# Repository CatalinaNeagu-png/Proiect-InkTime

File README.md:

# Proiect-InkTime
## 1. Diagrama Bloc a Sistemului
Diagrama de mai jos arata cum sunt conectate componentele principale la microcontroller-ul nRF52840:

- **Alimentare:** USB-C -> BQ25180 (Charger) -> Baterie LiPo 400mAh.
- **Afisaj:** Ecran E-Paper 1.54 inch (Conectat prin SPI).
- **Senzori:** Accelerometru BMA423 (Conectat prin I2C).
- **Haptica:** Driver DRV2605 + Motor Vibratii (Conectat prin I2C).
- **Interactiune:** 3 Butoane Tactile (Conectate prin GPIO).

## 2. Bill of Materials (BOM)
Componente selectate din catalogul JLCPCB:

| Componenta | Producator | JLC Part Number | Datasheet |
| :--- | :--- | :--- | :--- |
| MCU nRF52840 | Nordic Semi | C190733 | [Datasheet](https://infocenter.nordicsemi.com/pdf/nRF52840_PS_v1.0.pdf) |
| Senzor BMA423 | Bosch | C404044 | [Datasheet](https://www.bosch-sensortec.com/media/boschsensortec/downloads/datasheets/bst-bma423-ds004.pdf) |
| Charger BQ25180 | TI | C2907481 | [Datasheet](https://www.ti.com/lit/ds/symlink/bq25180.pdf) |
| Driver DRV2605L | TI | C63523 | [Datasheet](https://www.ti.com/lit/ds/symlink/drv2605l.pdf) |
| Antena 2.45GHz | Johanson | C105252 | [Datasheet](https://www.johansontechnology.com/datasheets/2450AT18B100.pdf) |

## 3. Functionalitate Hardware
Dispozitivul foloseste nRF52840 pentru gestionarea comunicatiei Bluetooth Low Energy.

- **Display E-Paper:** Foloseste interfata **SPI**. Avantajul principal este consumul de energie zero cand imaginea este statica.
- **Senzori:** Accelerometrul BMA423 (interfata **I2C**) detecteaza miscarea si pasii.
- **Haptica:** Driverul DRV2605L (interfata **I2C**) controleaza motorul de vibratii pentru alerte.
- **Consum:** S-a calculat un consum in standby de aproximativ 20uA, ceea ce asigura o durata de viata a bateriei de peste 30 de zile.

## 4. Mapare Pini nRF52840

| Functie | Pin nRF | Interfata | Justificare |
| :--- | :--- | :--- | :--- |
| SPI SCK | P0.20 | SPI | Ceas pentru ecran |
| SPI MOSI | P0.21 | SPI | Date pentru ecran |
| SPI CS | P0.22 | SPI | Selectie ecran |
| I2C SDA | P0.26 | I2C | Date senzori/charger |
| I2C SCL | P0.27 | I2C | Ceas senzori/charger |
| Buton Sus | P0.11 | GPIO | Intrare navigare |
| Buton OK | P0.12 | GPIO | Intrare selectie |
| Buton Jos | P0.13 | GPIO | Intrare navigare |

## 5. Design si Integrare Mecanica
- **Aliniere:** Butoanele tactile sunt plasate la Y=3mm pentru a se potrivi cu decupajele carcasei WearAware.
- **Antena:** Are o zona dedicata "keep-out" fara cupru pentru a nu bloca semnalul Bluetooth.
- **Asamblare:** Componentele sunt asezate tip "sandwich": Carcasa -> Display -> PCB -> Baterie.

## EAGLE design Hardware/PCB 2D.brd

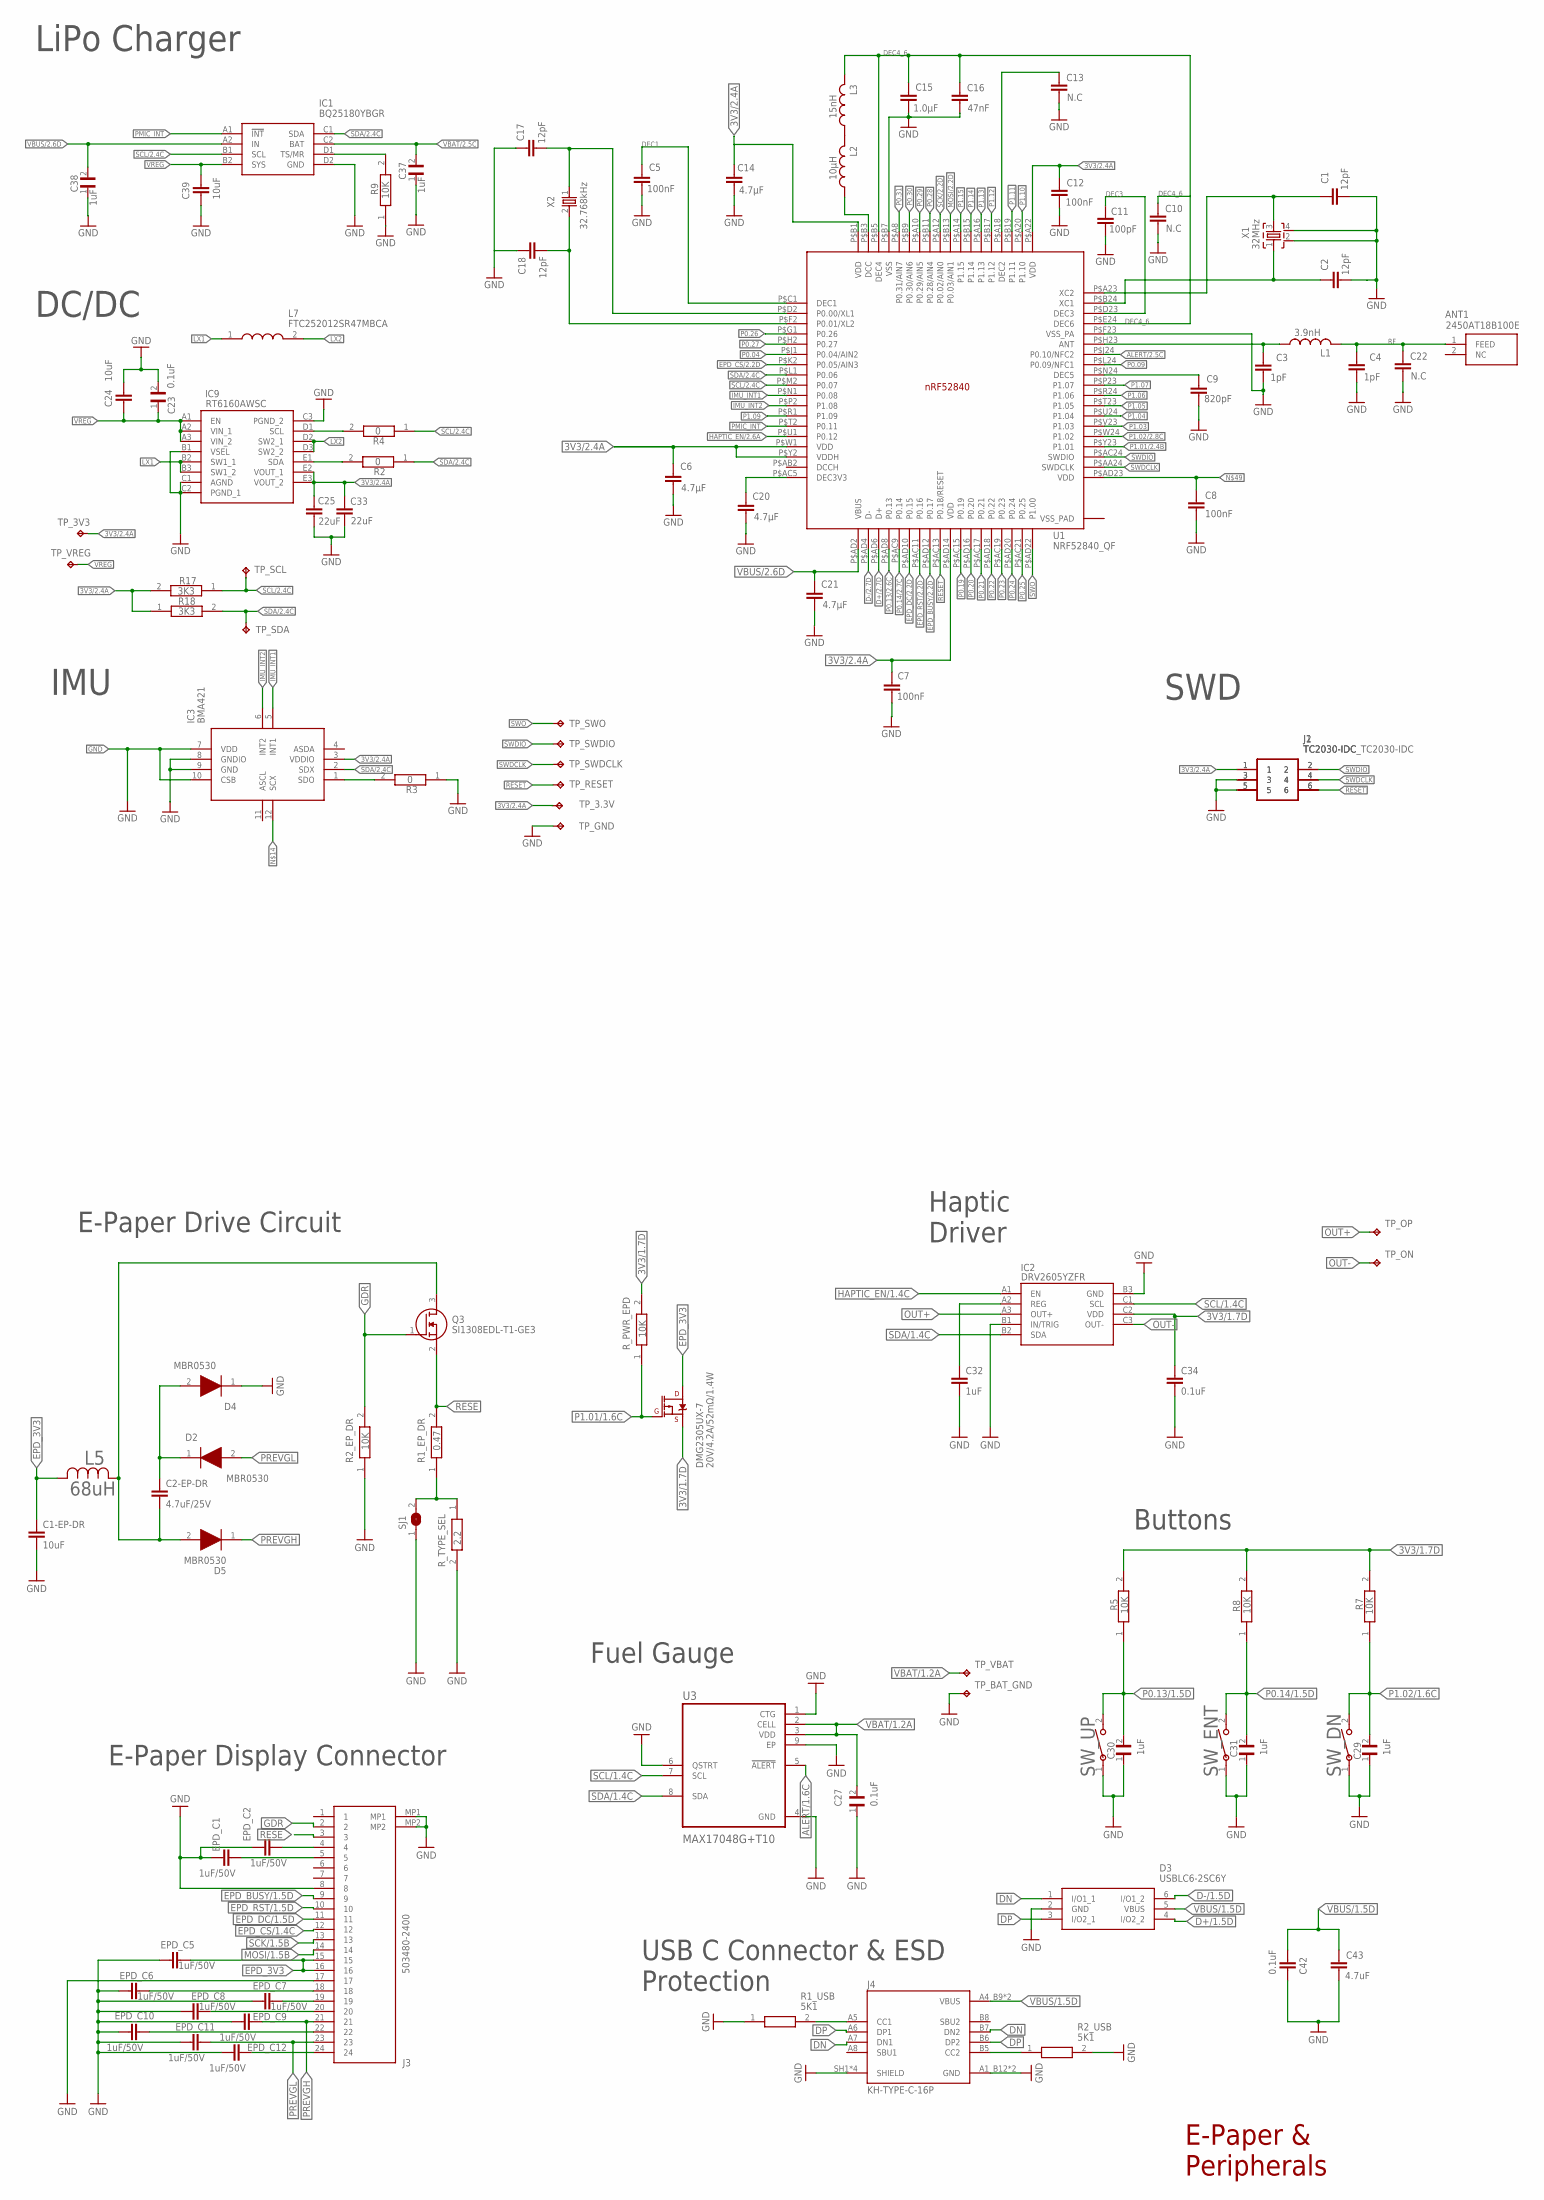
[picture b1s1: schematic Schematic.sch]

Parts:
ANT1: 2450AT18B100E; 2450AT18B100E_ANTC3216X140N
C1, C2, C17, C18: 12pF; NORDIC_NRF_3_RESC0201_L
C1-EP-DR: 10uF; ESP32_C6_LIBRARY_1_ESP32_WROVER_EAGLE-LTSPICE_C0402
C2-EP-DR: 4.7uF/25V; ESP32_C6_LIBRARY_1_ESP32_WROVER_EAGLE-LTSPICE_C0402
C3, C4: 1pF; NORDIC_NRF_3_RESC0201_L
C5, C7, C8, C12: 100nF; NORDIC_NRF_3_RESC0201_L
C6, C14, C20, C21: 4.7µF; NORDIC_NRF_3_RESC0201_L
C9: 820pF; NORDIC_NRF_3_RESC0201_L
C10, C13, C22: N.C; NORDIC_NRF_3_RESC0201_L
C11: 100pF; NORDIC_NRF_3_RESC0201_L
C15: 1.0µF; NORDIC_NRF_3_RESC0201_L
C16: 47nF; NORDIC_NRF_3_RESC0201_L
C23: 0.1uF; GRM011R60J152KE01L_1_0201
C24, C39: 10uF; NORDIC_NRF_3_RESC0201_L
C25, C33: 22uF; NORDIC_NRF_3_RESC0201_L
C27: 0.1uF; GRM011R60J152KE01L_2_CAPC0201X13N
C29, C30, C31: 1uF; GRM011R60J152KE01L_2_CAPC0201X13N
C32: 1uF; ESP32_C6_LIBRARY_1_ESP32_WROVER_EAGLE-LTSPICE_C0402
C34, C42: 0.1uF; ESP32_C6_LIBRARY_1_ESP32_WROVER_EAGLE-LTSPICE_C0402
C37, C38: 1uF; GRM011R60J152KE01L_1_0201
C43: 4.7uF; ESP32_C6_LIBRARY_1_ESP32_WROVER_EAGLE-LTSPICE_C0402
D2, D4: MBR0530; ESP32_C6_LIBRARY_5_SOD3716X135N
D3: USBLC6-2SC6Y; ESP32_C6_LIBRARY_3_SOT95P280X145-6N
DMG2305UX-7: 20V/4.2A/52mΩ/1.4W; ESP32_C6_LIBRARY_4_ESP32_C6_LIBRARY_4_ESP32_C6_LIBRARY_4_ES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
EPD_C1, EPD_C2, EPD_C5, EPD_C6, EPD_C7, EPD_C8, EPD_C9, EPD_C10, EPD_C11, EPD_C12: 1uF/50V; ESP32_C6_LIBRARY_1_ESP32_WROVER_EAGLE-LTSPICE_C0402
IC1: BQ25180YBGR; BQ25180YBGR_BGA8C40P2X4_100X155X50
IC2: DRV2605YZFR; DRV2605YZFR_BGA9C50P3X3_144X144X62
IC3: BMA421; BMA423_BMA423
IC9: RT6160AWSC; RT6160AWSC_BGA15C40P3X5_140X230X60
J1: TC2030-IDC_TC2030-IDC; TC2030-IDC_TC2030IDC
J2: TC2030-IDC; TC2030-IDC_TC2030IDC
J3: 503480-2400; 503480-2400_5034802400
J4: KH-TYPE-C-16P; KH-TYPE-C-16P_KINGHELM_KH-TYPE-C-16P
L1: 3.9nH; NORDIC_NRF_2_RESC0402_L
L2: 10µH; NORDIC_NRF_2_RESC0402_L
L3: 15nH; NORDIC_NRF_2_RESC0402_L
L5: 68uH; ESP32_C6_LIBRARY_2_IND_4828-WE-TPC_WRE
L7: FTC252012SR47MBCA; MLP2016SR47MT0S1_INDC2016X100N
MBR0530: D5; ESP32_C6_LIBRARY_5_SOD3716X135N
Q3: SI1308EDL-T1-GE3; ESP32_C6_LIBRARY_6_SOT65P210X110-3N
R1_EP_DR: 0.47; CPF0201D7K68C1_0201
R1_USB, R2_USB: 5K1; CPF0201D7K68C1_0201
R2, R3, R4: 0; CPF0201D7K68C1_0201
R2_EP_DR, R5, R7, R8, R9: 10K; CPF0201D7K68C1_0201
R17, R18: 3K3; CPF0201D7K68C1_0201
R_PWR_EPD: 10K; CPF0201D7K68C1_0201
R_TYPE_SEL: 2.2; CPF0201D7K68C1_0201
SJ1: ESP32_C6_LIBRARY_7_JUMPER_SJ
SW_DN: 2025-10-22_07-23-44_LIBRARY_EVP-AKE31ASW_EVP-AKE3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; 2025-10-22_07-23-44_LIBRARY_SW_EVP-AKE31A_PAN
SW_ENT: 2025-10-22_07-23-44_LIBRARY_EVP-AKE31ASW_EVP-AKE3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; 2025-10-22_07-23-44_LIBRARY_SW_EVP-AKE31A_PAN
SW_UP: 2025-10-22_07-23-44_LIBRARY_EVP-AKE31ASW_EVP-AKE3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; 2025-10-22_07-23-44_LIBRARY_SW_EVP-AKE31A_PAN
TP_3.3V, TP_3V3: HECTOR_WATCH_1_TPTP20R; HECTOR_WATCH_1_TP20R
TP_BAT_GND: HECTOR_WATCH_1_TPTP20R; HECTOR_WATCH_1_TP20R
TP_GND: HECTOR_WATCH_1_TPTP20R; HECTOR_WATCH_1_TP20R
TP_ON: HECTOR_WATCH_1_TPTP20R; HECTOR_WATCH_1_TP20R
TP_OP: HECTOR_WATCH_1_TPTP20R; HECTOR_WATCH_1_TP20R
TP_RESET: HECTOR_WATCH_1_TPTP20R; HECTOR_WATCH_1_TP20R
TP_SCL: HECTOR_WATCH_1_TPTP20R; HECTOR_WATCH_1_TP20R
TP_SDA: HECTOR_WATCH_1_TPTP20R; HECTOR_WATCH_1_TP20R
TP_SWDCLK: HECTOR_WATCH_1_TPTP20R; HECTOR_WATCH_1_TP20R
TP_SWDIO: HECTOR_WATCH_1_TPTP20R; HECTOR_WATCH_1_TP20R
TP_SWO: HECTOR_WATCH_1_TPTP20R; HECTOR_WATCH_1_TP20R
TP_VBAT: HECTOR_WATCH_1_TPTP20R; HECTOR_WATCH_1_TP20R
TP_VREG: HECTOR_WATCH_1_TPTP20R; HECTOR_WATCH_1_TP20R
U1: NRF52840_QF; NORDIC_NRF_4_AQFN50P700X700X85_HS-74N
U3: MAX17048G+T10; ESP32_C6_LIBRARY_SON50P200X200X80-9N
X1: 32MHz; NORDIC_NRF_BT-XTAL_2016_N
X2: 32.768kHz; NORDIC_NRF_1_XTAL_3215_N

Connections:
3V3/1.7D: C34.1, DMG2305UX-7.2 (S), IC2.C2 (VDD), R5.2, R7.2, R8.2, R_PWR_EPD.2
3V3/2.4A: C6.1, C25.1, IC3.3 (VDDIO), IC9.E2 (VOUT_1), IC9.E3 (VOUT_2), J1.1, J2.1, R17.2, R18.1, U1.P$A22 (VDD), U1.P$AD14 (VDD), U1.P$W1 (VDD)
ALERT/1.6C: U3.5 (!ALERT)
ALERT/2.5C: U1.P$J24 (P0.10/NFC2)
D+/1.5D: D3.4 (I/O2_2)
D+/2.7D: U1.P$AD6 (D+)
D-/1.5D: D3.6 (I/O1_2)
D-/2.7D: U1.P$AD4 (D-)
DEC1: C5.1, U1.P$C1 (DEC1)
DEC3: C11.1, U1.P$D23 (DEC3)
DEC4_6: C10.1, L3.2, U1.P$E24 (DEC6)
DN: D3.1 (I/O1_1), J4.A7 (DN1), J4.B7 (DN2)
DP: D3.3 (I/O2_1), J4.A6 (DP1), J4.B6 (DP2)
EPD_3V3: C1-EP-DR.1, DMG2305UX-7.3 (D), EPD_C5.2, J3.15, J3.16, L5.2
EPD_BUSY/1.5D: J3.9
EPD_BUSY/2.2D: U1.P$AD12 (P0.17)
EPD_CS/1.4C: J3.12
EPD_CS/2.2D: U1.P$K2 (P0.05/AIN3)
EPD_DC/1.5D: J3.11
EPD_DC/2.2D: U1.P$AD10 (P0.15)
EPD_RST/1.5D: J3.10
EPD_RST/2.2D: U1.P$AC11 (P0.16)
GDR: J3.2, Q3.1 (G), R2_EP_DR.2
GND: C1.2, C1-EP-DR.2, C3.2, C4.2, C5.2, C6.2, C7.2, C8.2, C9.2, C10.2, C11.2, C12.2, C13.2, C14.2, C15.2, C17.1, C20.2, C21.2, C22.2, C23.2, C24.1, C25.2, C27.1, C29.1, C30.1, C31.1, C32.2, C33.2, C34.2, C37.1, C38.1, C39.2, C42.2, C43.1, D3.2 (GND), D4.1 (K), EPD_C1.1, EPD_C2.1, EPD_C5.1, EPD_C6.1, EPD_C7.1, EPD_C8.1, EPD_C9.1, EPD_C10.1, EPD_C11.1, EPD_C12.1, IC1.D2 (GND), IC2.B1 (IN/TRIG), IC2.B3 (GND), IC3.7 (VDD), IC3.10 (CSB), IC9.B1 (VSEL), IC9.C1 (AGND), IC9.C2 (PGND_1), IC9.C3 (PGND_2), J1.3, J1.5, J2.3, J2.5, J3.8, J3.17, J3.MP1, J3.MP2, J4.A1_B12 (GND), J4.A12_B1 (GND), J4.SH1 (SHIELD), J4.SH2 (SHIELD), J4.SH3 (SHIELD), J4.SH4 (SHIELD), R1_USB.1, R2_EP_DR.1, R2_USB.2, R3.1, R9.1, R_TYPE_SEL.2, SJ1.1, SW_DN.1, SW_ENT.1, SW_UP.1, TP_BAT_GND.TP, U3.1 (CTG), U3.4 (GND), U3.6 (QSTRT), U3.9 (EP)
HAPTIC_EN/1.4C: IC2.A1 (EN)
HAPTIC_EN/2.6A: U1.P$U1 (P0.12)
IMU_INT1: IC3.5 (INT1), U1.P$N1 (P0.08)
IMU_INT2: IC3.6 (INT2), U1.P$P2 (P1.08)
LX1: IC9.B2 (SW1_1), IC9.B3 (SW1_2), L7.1
LX2: IC9.D2 (SW2_1), IC9.D3 (SW2_2), L7.2
MOSI/1.5B: J3.14
MOSI/2.2D: U1.P$B13 (P0.03/AIN1)
unnamed: IC1.D1 (TS/MR), R9.2
unnamed: IC9.D1 (SCL), R4.2
unnamed: IC9.E1 (SDA), R2.2
unnamed: IC3.8 (GNDIO), IC3.9 (GND)
unnamed: IC3.1 (SDO), R3.2
unnamed: C2-EP-DR.2, L5.1, MBR0530.2 (A), Q3.3 (D)
unnamed: R18.2, TP_SDA.TP
unnamed: C14.1, U1.P$B1 (VDD)
unnamed: L2.2, L3.1
unnamed: U1.P$D2 (P0.00/XL1), X2.1
unnamed: U1.P$F2 (P0.01/XL2), X2.2
unnamed: C20.1, U1.P$AC5 (DEC3V3)
unnamed: C2-EP-DR.1, D2.1 (K), D4.2 (A)
unnamed: L2.1, U1.P$B3 (DCC)
unnamed: C16.2, U1.P$B7 (VSS)
unnamed: C13.1, U1.P$A18 (DEC2)
unnamed: C1.1, U1.P$A23 (XC2)
unnamed: C2.1, U1.P$B24 (XC1)
unnamed: C9.1, U1.P$N24 (DEC5)
unnamed: L1.1, U1.P$H23 (ANT)
unnamed: R1_EP_DR.1, R_TYPE_SEL.1, SJ1.2
unnamed: C32.1, IC2.A2 (REG)
unnamed: EPD_C2.2, J3.4
unnamed: EPD_C1.2, J3.5
unnamed: EPD_C7.2, J3.19
unnamed: EPD_C8.2, J3.20
unnamed: EPD_C10.2, J3.22
unnamed: EPD_C12.2, J3.24
unnamed: EPD_C6.2, J3.18
unnamed: J4.A5 (CC1), R1_USB.2
unnamed: J4.B5 (CC2), R2_USB.1
OUT+: IC2.A3 (OUT+), TP_OP.TP
OUT-: IC2.C3 (OUT-), TP_ON.TP
P0.04: U1.P$J1 (P0.04/AIN2)
P0.09: U1.P$L24 (P0.09/NFC1)
P0.13/1.5D: C30.2, R5.1, SW_UP.2
P0.13/2.6C: U1.P$AD8 (P0.13)
P0.14/1.5D: C31.2, R8.1, SW_ENT.2
P0.14/2.7C: U1.P$AC9 (P0.14)
P0.19: U1.P$AC15 (P0.19)
P0.20: U1.P$AD16 (P0.20)
P0.21: U1.P$AC17 (P0.21)
P0.22: U1.P$AD18 (P0.22)
P0.23: U1.P$AC19 (P0.23)
P0.24: U1.P$AD20 (P0.24)
P0.25: U1.P$AC21 (P0.25)
P0.26: U1.P$G1 (P0.26)
P0.27: U1.P$H2 (P0.27)
P0.28: U1.P$B11 (P0.28/AIN4)
P0.29: U1.P$A10 (P0.29/AIN5)
P0.30: U1.P$B9 (P0.30/AIN6)
P0.31: U1.P$A8 (P0.31/AIN7)
P1.01/1.6C: DMG2305UX-7.1 (G), R_PWR_EPD.1
P1.01/2.4B: U1.P$Y23 (P1.01)
P1.02/1.6C: C29.2, R7.1, SW_DN.2
P1.02/2.8C: U1.P$W24 (P1.02)
P1.03: U1.P$V23 (P1.03)
P1.04: U1.P$U24 (P1.04)
P1.05: U1.P$T23 (P1.05)
P1.06: U1.P$R24 (P1.06)
P1.07: U1.P$P23 (P1.07)
P1.09: U1.P$R1 (P1.09)
P1.10: U1.P$A20 (P1.10)
P1.11: U1.P$B19 (P1.11)
P1.12: U1.P$B17 (P1.12)
P1.13: U1.P$A16 (P1.13)
P1.14: U1.P$B15 (P1.14)
P1.15: U1.P$A14 (P1.15)
PMIC_INT: IC1.A1 (!INT), U1.P$T2 (P0.11)
PREVGH: EPD_C9.2, J3.21, MBR0530.1 (K)
PREVGL: D2.2 (A), EPD_C11.2, J3.23
RESE: J3.3, Q3.2 (S), R1_EP_DR.2
RESET: J1.6, J2.6, U1.P$AC13 (P0.18/RESET)
RF: ANT1.1 (FEED), L1.2
SCK/1.5B: J3.13
SCK/2.2D: U1.P$A12 (P0.02/AIN0)
SCL/1.4C: IC2.C1 (SCL), U3.7 (SCL)
SCL/2.4C: IC1.B1 (SCL), R4.1, R17.1, U1.P$M2 (P0.07)
SDA/1.4C: IC2.B2 (SDA), U3.8 (SDA)
SDA/2.4C: IC1.C1 (SDA), IC3.2 (SDX), R2.1, U1.P$L1 (P0.06)
SWDCLK: J1.4, J2.4, U1.P$AA24 (SWDCLK)
SWDIO: J1.2, J2.2, U1.P$AC24 (SWDIO)
SWO: U1.P$AD22 (P1.00)
VBAT/1.2A: C27.2, TP_VBAT.TP, U3.2 (CELL), U3.3 (VDD)
VBAT/2.5C: C37.2, IC1.C2 (BAT)
VBUS/1.5D: C42.1, C43.2, D3.5 (VBUS), J4.A4_B9 (VBUS), J4.A9_B4 (VBUS)
VBUS/2.6D: C38.2, IC1.A2 (IN), U1.P$AD2 (VBUS)
VREG: C39.1, IC1.B2 (SYS), IC9.A1 (EN), IC9.A2 (VIN_1), IC9.A3 (VIN_2)

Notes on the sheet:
LiPo Charger
DC/DC
IMU
SWD
E-Paper Drive Circuit
E-Paper Display Connector
Fuel Gauge
Buttons
USB C Connector & ESD Protection
Haptic Driver
E-Paper & Peripherals

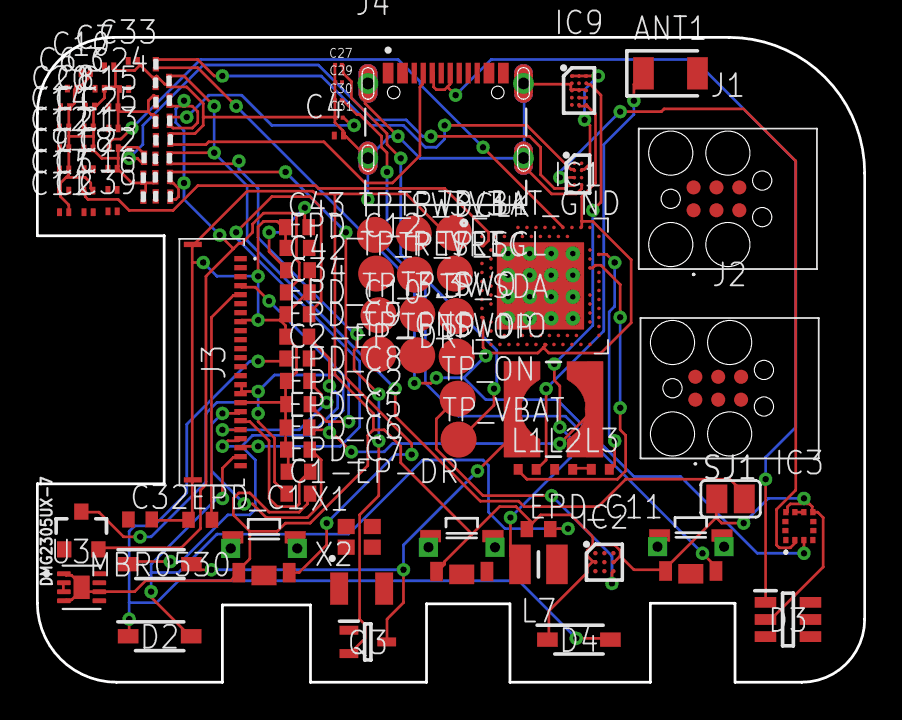
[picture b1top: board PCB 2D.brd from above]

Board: 2 copper layers, 46.0 x 35.8 mm, 105 parts (0 on the bottom side), 68 nets.

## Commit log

2026-04-10 README
    Added detailed project description, technical specifications, design decisions, and repository structure.
2026-04-10 Create hardware
2026-04-10 Create test
2026-04-10 readme
2026-04-20 Rename Diagram.jpg.png to Diagram.jpg

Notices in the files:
parts and their libraries:
COPYRIGHT: Copyright (C) 2024 Ultra Librarian. All rights reserved.
COPYRIGHT: Copyright (C) 2025 Ultra Librarian. All rights reserved.
